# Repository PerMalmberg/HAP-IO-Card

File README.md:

# HAP I/O Card
Input/output card for use in automation

## Design limits
12V maximum voltage.

## Inputs

### Analog inputs

On-board potentiometers as voltage dividers, allowing for adjustable balanced lines used in alarm systems.
> Will fixed resistors do the trick?

### Digital Inputs

* Optocouplers to provide isolation.
* On-board rotary switch to set number of inputs.
* On-board rotary switch to set unit MQTT address.

> Can it be done so that from a software perspective they are always high/true when 'activated'?

## Outputs

### Digital Outputs

* Optocoupler for low current signals.
* Relays for high-current signals.
* Each output shall have a LED indicating current status.

### General in/outputs

UART flashing connectors.
Debugging pins/JTAG

## On-board LEDs
* Power
* Digital outputs
* Digital inputs

## On-board switches
* OTA-enable

## Power supply
12V DC, with onboard 12->5V DC/DC converter.

## Reference Links

http://www.thebox.myzen.co.uk/Tutorial/Protection.html

* Capacitor calculations
  * http://www.electronics-tutorials.ws/rc/rc_1.html

### Components

#### uC ESP32 thing devboard
  * http://www.mouser.se/new/sparkfun/sparkfun-things/

* Common components
  * 10k ohm 0805 0.5W https://www.digikey.se/product-detail/en/panasonic-electronic-components/ERJ-P06F1002V/P16059CT-ND/3982406
  * 100nF 50V https://www.digikey.se/product-detail/en/avx-corporation/08055C104JAT2A/478-3352-1-ND/930144

* Sensor Inputs
  * I/O Expander ADS1115IDGST https://www.digikey.se/product-detail/en/texas-instruments/ADS1115IDGST/296-24934-1-ND/2123298
  * Varistor 39V 0805 https://www.digikey.se/product-detail/en/epcos-tdk/B72510E250K62/495-7453-1-ND/6073112
  * 2k resistor, 0.5W 0805 https://www.digikey.se/product-detail/en/panasonic-electronic-components/ERJ-P06F2001V/P16065CT-ND/3982412
  * Clamping Shottky diodes 60V, 500mA SOD-123 https://www.digikey.se/product-detail/en/stmicroelectronics/STPS0560Z/497-3787-1-ND/691956
  * Protection diode 3A, SMA https://www.digikey.se/product-detail/en/comchip-technology/CDBA3100-HF/641-1747-1-ND/5400721
  * 100 ohm 1/8W 0805 https://www.digikey.se/product-detail/en/yageo/RC0805FR-07100RL/311-100CRCT-ND/730490
  * 1k ohm 0.5W 0805 https://www.digikey.se/product-detail/en/vishay-dale/CRCW08051K00FKEAHP/541-1.00KTCT-ND/2222852

* Digital I/O
  * I/O Expander MCP23017 https://www.digikey.se/product-detail/en/microchip-technology/MCP23017T-E-SO/MCP23017T-E-SOCT-ND/5358289
  * Input      
    * LED Green Vf 2.2, 20mA https://www.digikey.se/product-detail/en/lumex-opto-components-inc/SML-LXR85GC-TR/67-1557-1-ND/304376
    * LED limiting resistor 56R, 1/8W, 0805 https://www.digikey.se/product-detail/en/panasonic-electronic-components/ERJ-6GEYJ560V/P56ACT-ND/42928
    * 100R discharge resistor https://www.digikey.se/product-detail/en/stackpole-electronics-inc/RNCP0805FTD100R/RNCP0805FTD100RCT-ND/2240548
    * 10uF Electrolytic Cap https://www.digikey.se/product-detail/en/panasonic-electronic-components/EEE-1EA100WR/PCE3895CT-ND/766271
    * 1k 3W, 1%, 2512 https://www.digikey.se/product-detail/en/te-connectivity-passive-product/35221K0FT/A121161CT-ND/5245218
    * LTV-354T https://www.digikey.se/product-detail/en/lite-on-inc/LTV-354T/160-1333-1-ND/385797
  * Output
    * Base resistor 470 http://www.digikey.se/scripts/DkSearch/dksus.dll?Detail&itemSeq=230677912&uq=636330538988753686
    * Kickback protection MBR0580 https://www.digikey.se/product-detail/en/micro-commercial-co/MBR0580-TP/MBR0580-TPMSCT-ND/2423306
    * Transistor https://www.digikey.se/product-detail/en/diodes-incorporated/ZXTN25050DFHTA/ZXTN25050DFHCT-ND/1043605
    * LED RED 20mA, Vf 2V https://www.digikey.se/product-detail/en/lumex-opto-components-inc/SML-LXR85IC-TR/67-1556-1-ND/304374
    * LED limiting resistor 68R, 1/8W, 0805 https://www.digikey.se/product-detail/en/stack  pole-electronics-inc/RMCF0805JT68R0/RMCF0805JT68R0CT-ND/1942537

* Power supply
  * Screw terminal 3-way https://www.digikey.se/product-detail/en/te-connectivity-amp-connectors/282834-3/A98334-ND/1153264
  * LM1086-5V https://www.digikey.se/product-detail/en/texas-instruments/LM1086IT-5.0-NOPB/LM1086IT-5.0-NOPB-ND/363580
  * LM1086-3.3V https://www.digikey.se/product-detail/en/texas-instruments/LM1086IT-3.3-NOPB/LM1086IT-3.3-NOPB-ND/363579
  * 100uF 16V 5mm https://www.digikey.se/product-detail/en/nichicon/ULD1C101MED1TD/493-14722-1-ND/6161730
  * Protection diode MBRS360BT3G http://www.digikey.se/scripts/DkSearch/dksus.dll?Detail&itemSeq=230549693&uq=636329621710320791
  * Zener 5.1V SOD-123 https://www.digikey.se/products/en?keywords=1N4733AW-TPMSCT-ND
  * Signal filter https://www.digikey.se/product-detail/en/murata-electronics-north-america/DSS1NB31H104Q91A/490-9806-1-ND/5018359

https://www.facebook.com/groups/SHgruppen/permalink/662561353933301/?comment_id=662612023928234&reply_comment_id=662644947258275&notif_t=group_comment_reply&notif_id=1495821072857152

https://www.facebook.com/groups/SHgruppen/permalink/662561353933301/?comment_id=662622243927212&reply_comment_id=662650937257676&comment_tracking=%7B%22tn%22%3A%22R5%22%7D

## TODO
Fuse 12V and 3.3V PolyFuse

I2C jumpers to disable devices (development feature)?
ESD protection on in/outputs
Display
Flashing wires
Mounting holes http://www.ebay.com/itm/DIN-Rail-Mounting-Carrier-for-72mm-x-110mm-PCB-Housing-Bracket-/131318695142
I2C expansion header
Test points

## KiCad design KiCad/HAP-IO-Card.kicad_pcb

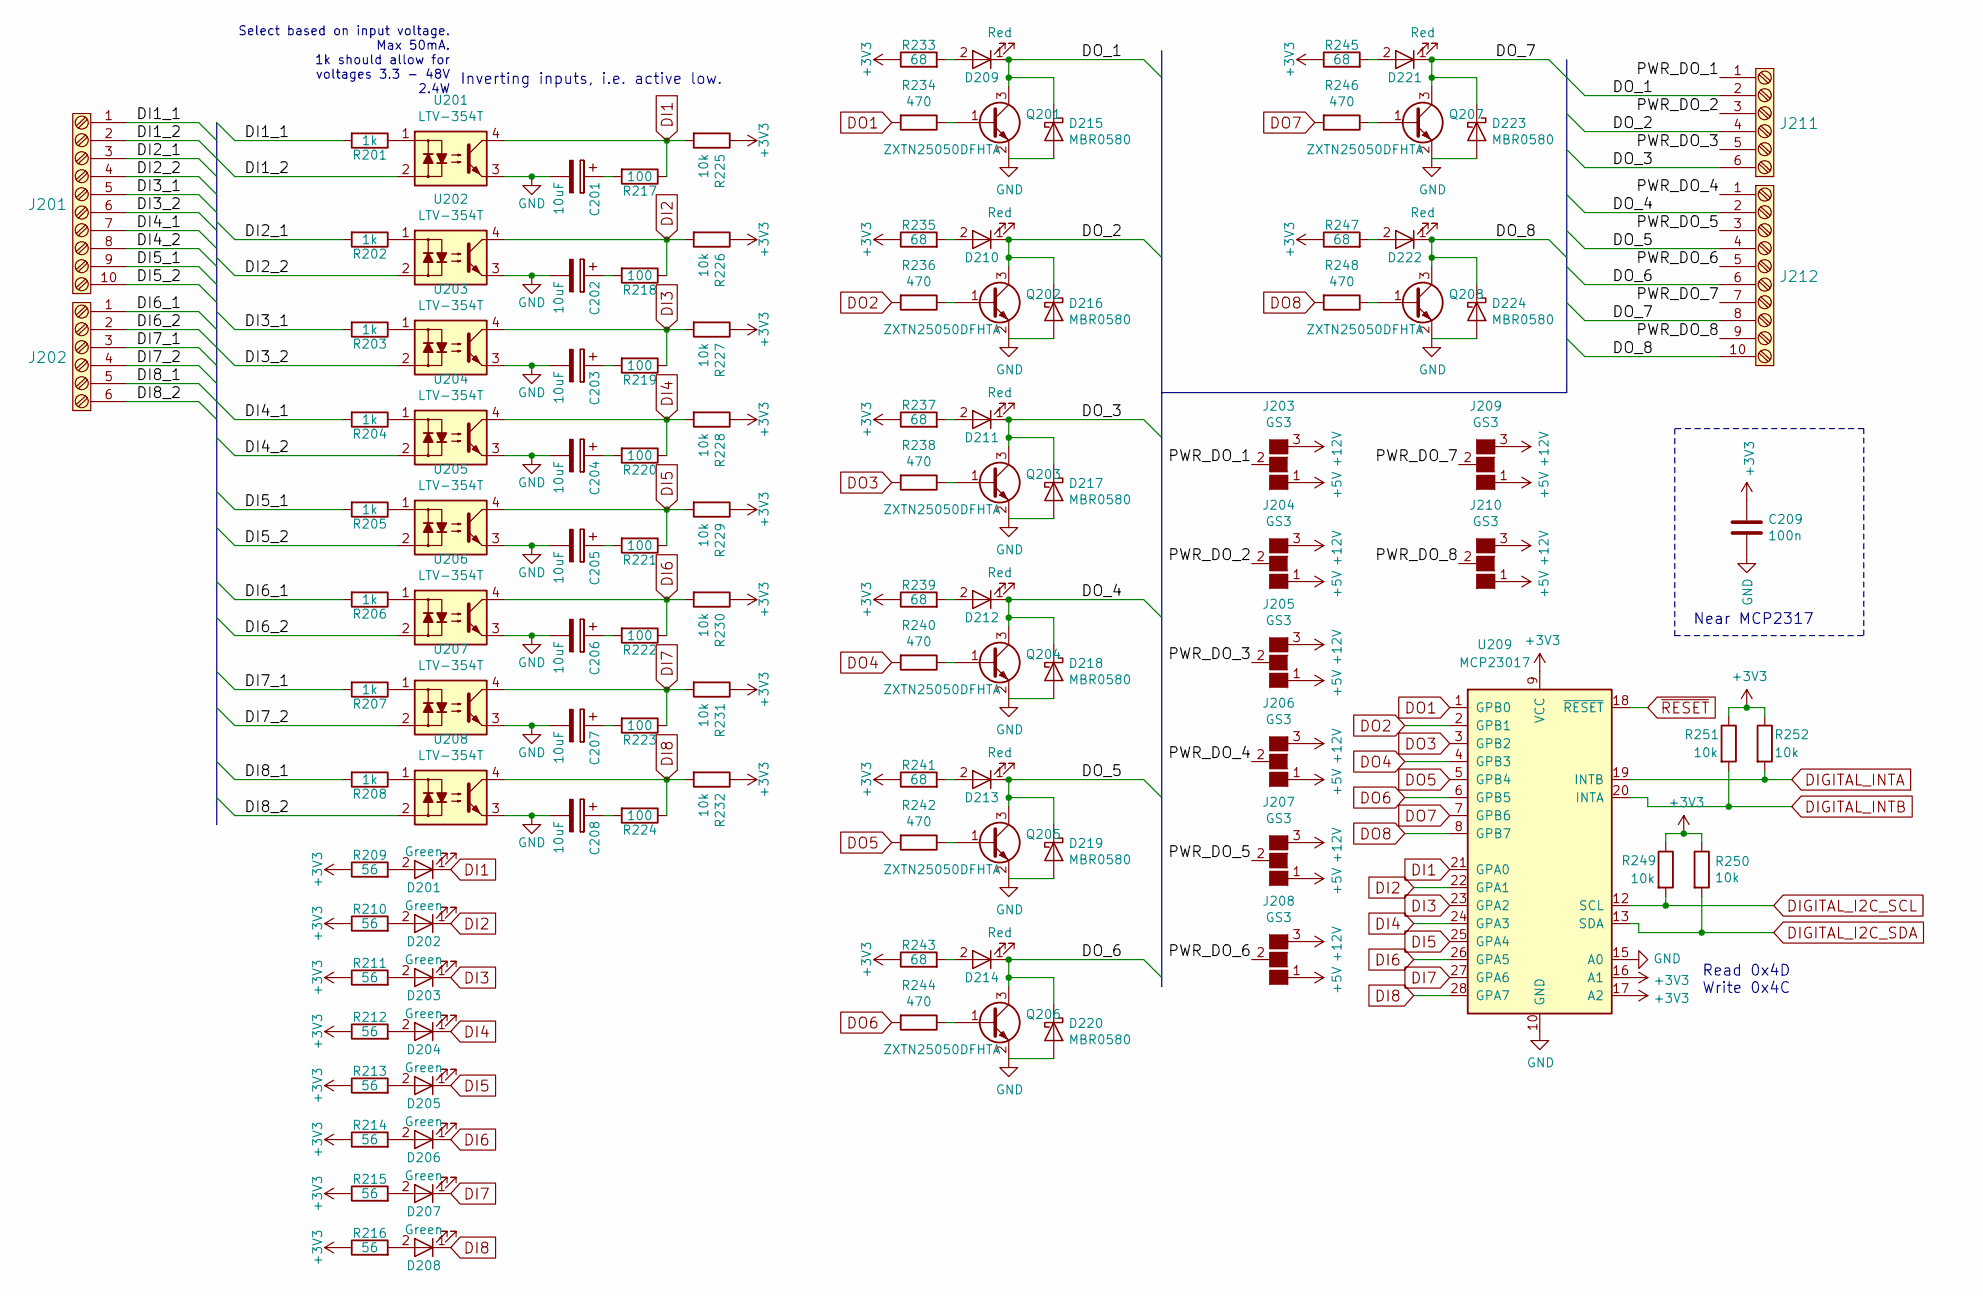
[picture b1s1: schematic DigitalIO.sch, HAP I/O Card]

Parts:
C201, C202, C203, C204, C205, C206, C207, C208: 10uF; CP_Elec_5x4.5
C209: 100n; C_0805
D201, D202, D203, D204, D205, D206, D207, D208: Green; LED_0805
D209, D210, D211, D212, D213, D214, D221, D222: Red; LED_0805
D215, D216, D217, D218, D219, D220, D223, D224: MBR0580; D_SOD-123
J201, J212: TE_Connectivity_1-282834-0
J202, J211: TE_Connectivity_282834-6
J203, J204, J205, J206, J207, J208, J209, J210: GS3
Q201, Q202, Q203, Q204, Q205, Q206, Q207, Q208: ZXTN25050DFHTA; SOT-23
R201, R202, R203, R204, R205, R206, R207, R208: 1k; R_2512
R209, R210, R211, R212, R213, R214, R215, R216: 56; R_0805
R217, R218, R219, R220, R221, R222, R223, R224: 100; R_0805
R225, R226, R227, R228, R229, R230, R231, R232, R249, R250, R251, R252: 10k; R_0805
R233, R235, R237, R239, R241, R243, R245, R247: 68; R_0805
R234, R236, R238, R240, R242, R244, R246, R248: 470; R_0805
U201, U202, U203, U204, U205, U206, U207, U208: LTV-354T; SO-4_4.4x3.6mm_Pitch2.54mm
U209: MCP23017; SOIC-28W_7.5x17.9mm_Pitch1.27mm

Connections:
+12V: J203.3 (G3), J204.3 (G3), J205.3 (G3), J206.3 (G3), J207.3 (G3), J208.3 (G3), J209.3 (G3), J210.3 (G3); also elsewhere on the board
/Digital I/O/DI1_1: J201.1, R201.2
/Digital I/O/DI1_2: J201.2, U201.2
/Digital I/O/DI2_1: J201.3, R202.2
/Digital I/O/DI2_2: J201.4, U202.2
/Digital I/O/DI3_1: J201.5, R203.2
/Digital I/O/DI3_2: J201.6, U203.2
/Digital I/O/DI4_1: J201.7, R204.2
/Digital I/O/DI4_2: J201.8, U204.2
/Digital I/O/DI5_1: J201.9, R205.2
/Digital I/O/DI5_2: J201.10, U205.2
/Digital I/O/DI6_1: J202.1, R206.2
/Digital I/O/DI6_2: J202.2, U206.2
/Digital I/O/DI7_1: J202.3, R207.2
/Digital I/O/DI7_2: J202.4, U207.2
/Digital I/O/DI8_1: J202.5, R208.2
/Digital I/O/DI8_2: J202.6, U208.2
/Digital I/O/DO_1: D209.1 (K), D215.1 (K), J211.2, Q201.3 (C)
/Digital I/O/DO_2: D210.1 (K), D216.1 (K), J211.4, Q202.3 (C)
/Digital I/O/DO_3: D211.1 (K), D217.1 (K), J211.6, Q203.3 (C)
/Digital I/O/DO_4: D212.1 (K), D218.1 (K), J212.2, Q204.3 (C)
/Digital I/O/DO_5: D213.1 (K), D219.1 (K), J212.4, Q205.3 (C)
/Digital I/O/DO_6: D214.1 (K), D220.1 (K), J212.6, Q206.3 (C)
/Digital I/O/DO_7: D221.1 (K), D223.1 (K), J212.8, Q207.3 (C)
/Digital I/O/DO_8: D222.1 (K), D224.1 (K), J212.10, Q208.3 (C)
/Digital I/O/PWR_DO_1: J203.2 (G2), J211.1
/Digital I/O/PWR_DO_2: J204.2 (G2), J211.3
/Digital I/O/PWR_DO_3: J205.2 (G2), J211.5
/Digital I/O/PWR_DO_4: J206.2 (G2), J212.1
/Digital I/O/PWR_DO_5: J207.2 (G2), J212.3
/Digital I/O/PWR_DO_6: J208.2 (G2), J212.5
/Digital I/O/PWR_DO_7: J209.2 (G2), J212.7
/Digital I/O/PWR_DO_8: J210.2 (G2), J212.9
DI1: D201.1 (K), R217.1, R225.2, U201.4, U209.21 (GPA0)
DI2: D202.1 (K), R218.1, R226.2, U202.4, U209.22 (GPA1)
DI3: D203.1 (K), R219.1, R227.2, U203.4, U209.23 (GPA2)
DI4: D204.1 (K), R220.1, R228.2, U204.4, U209.24 (GPA3)
DI5: D205.1 (K), R221.1, R229.2, U205.4, U209.25 (GPA4)
DI6: D206.1 (K), R222.1, R230.2, U206.4, U209.26 (GPA5)
DI7: D207.1 (K), R223.1, R231.2, U207.4, U209.27 (GPA6)
DI8: D208.1 (K), R224.1, R232.2, U208.4, U209.28 (GPA7)
DIGITAL_I2C_SCL: R249.2, U209.12 (SCL); also elsewhere on the board
DIGITAL_I2C_SDA: R250.2, U209.13 (SDA); also elsewhere on the board
DIGITAL_INTA: R252.2, U209.19 (INTB); also elsewhere on the board
DIGITAL_INTB: R251.2, U209.20 (INTA); also elsewhere on the board
DO1: R234.2, U209.1 (GPB0)
DO2: R236.2, U209.2 (GPB1)
DO3: R238.2, U209.3 (GPB2)
DO4: R240.2, U209.4 (GPB3)
DO5: R242.2, U209.5 (GPB4)
DO6: R244.2, U209.6 (GPB5)
DO7: R246.2, U209.7 (GPB6)
DO8: R248.2, U209.8 (GPB7)
Earth: C201.2, C202.2, C203.2, C204.2, C205.2, C206.2, C207.2, C208.2, C209.2, D215.2 (A), D216.2 (A), D217.2 (A), D218.2 (A), D219.2 (A), D220.2 (A), D223.2 (A), D224.2 (A), Q201.2 (E), Q202.2 (E), Q203.2 (E), Q204.2 (E), Q205.2 (E), Q206.2 (E), Q207.2 (E), Q208.2 (E), U201.3, U202.3, U203.3, U204.3, U205.3, U206.3, U207.3, U208.3, U209.10 (GND), U209.15 (A0); also elsewhere on the board
unnamed: C201.1, R217.2
unnamed: C202.1, R218.2
unnamed: C203.1, R219.2
unnamed: C204.1, R220.2
unnamed: C205.1, R221.2
unnamed: C206.1, R222.2
unnamed: C207.1, R223.2
unnamed: C208.1, R224.2
unnamed: D201.2 (A), R209.2
unnamed: D202.2 (A), R210.2
unnamed: D203.2 (A), R211.2
unnamed: D204.2 (A), R212.2
unnamed: D205.2 (A), R213.2
unnamed: D206.2 (A), R214.2
unnamed: D207.2 (A), R215.2
unnamed: D208.2 (A), R216.2
unnamed: D209.2 (A), R233.2
unnamed: D210.2 (A), R235.2
unnamed: D211.2 (A), R237.2
unnamed: D212.2 (A), R239.2
unnamed: D213.2 (A), R241.2
unnamed: D214.2 (A), R243.2
unnamed: D221.2 (A), R245.2
unnamed: D222.2 (A), R247.2
unnamed: Q201.1 (B), R234.1
unnamed: Q202.1 (B), R236.1
unnamed: Q203.1 (B), R238.1
unnamed: Q204.1 (B), R240.1
unnamed: Q205.1 (B), R242.1
unnamed: Q206.1 (B), R244.1
unnamed: Q207.1 (B), R246.1
unnamed: Q208.1 (B), R248.1
unnamed: R201.1, U201.1
unnamed: R202.1, U202.1
unnamed: R203.1, U203.1
unnamed: R204.1, U204.1
unnamed: R205.1, U205.1
unnamed: R206.1, U206.1
unnamed: R207.1, U207.1
unnamed: R208.1, U208.1
POWER3V3: C209.1, R209.1, R210.1, R211.1, R212.1, R213.1, R214.1, R215.1, R216.1, R225.1, R226.1, R227.1, R228.1, R229.1, R230.1, R231.1, R232.1, R233.1, R235.1, R237.1, R239.1, R241.1, R243.1, R245.1, R247.1, R249.1, R250.1, R251.1, R252.1, U209.9 (VCC), U209.16 (A1), U209.17 (A2); also elsewhere on the board
POWER5V: J203.1 (G1), J204.1 (G1), J205.1 (G1), J206.1 (G1), J207.1 (G1), J208.1 (G1), J209.1 (G1), J210.1 (G1); also elsewhere on the board
~RESET: U209.18 (~RESET); also elsewhere on the board

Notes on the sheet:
Select based on input voltage. Max 50mA. 1k should allow for voltages 3.3 - 48V 2.4W
Inverting inputs, i.e. active low.
Read 0x4D Write 0x4C
Near MCP2317

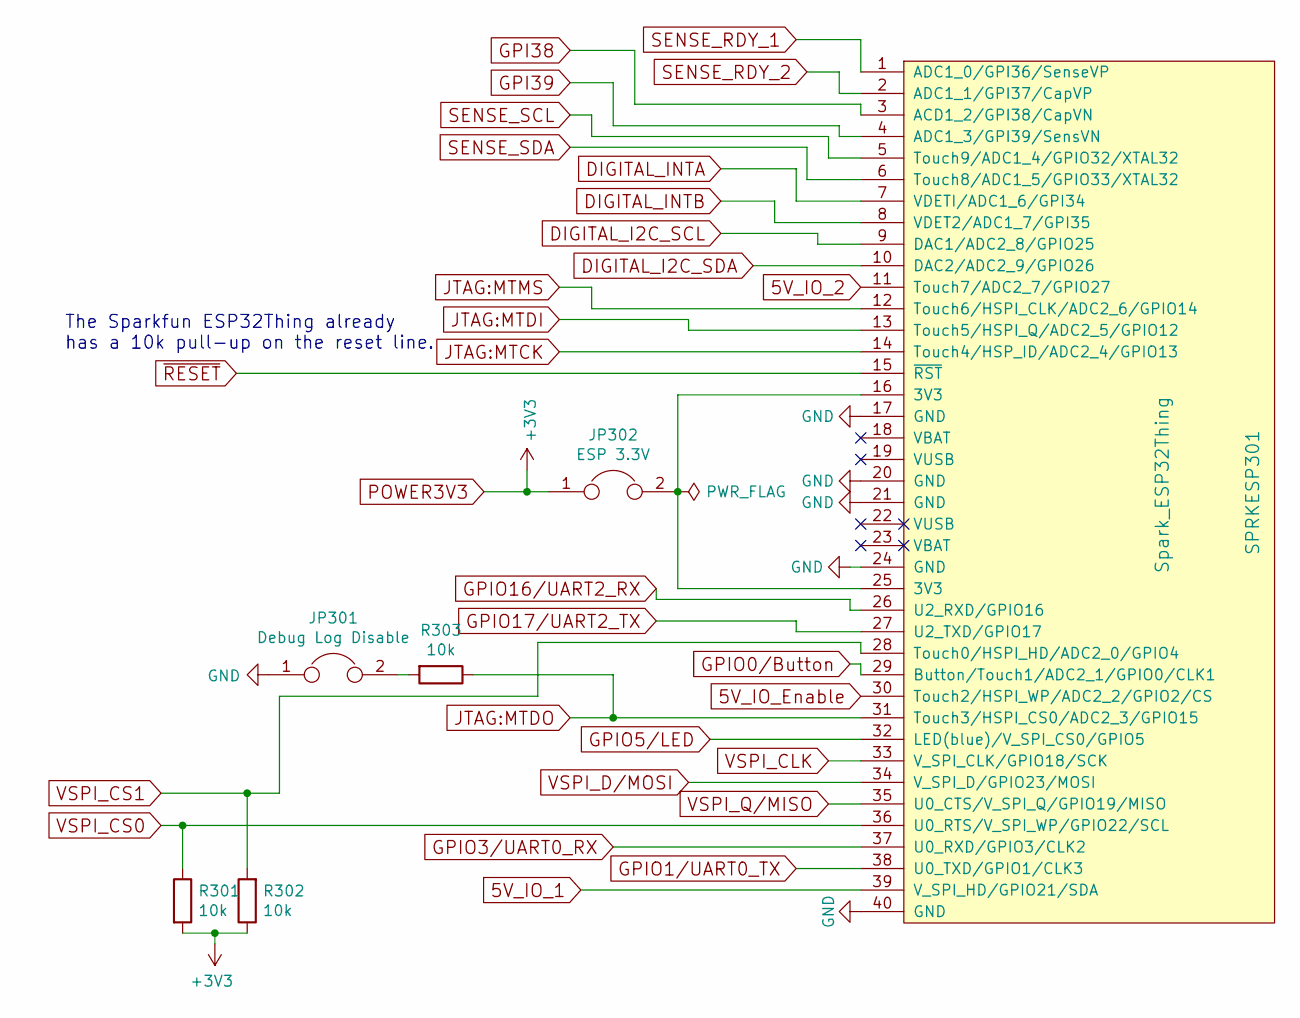
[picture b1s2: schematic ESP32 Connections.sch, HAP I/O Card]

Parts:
JP301: Debug Log Disable; Pin_Header_Straight_1x02_Pitch2.54mm
JP302: ESP 3.3V; Pin_Header_Straight_1x02_Pitch2.54mm
R301, R302, R303: 10k; R_0805
SPRKESP301: Spark_ESP32Thing; Sparkfun_ESP32Thing

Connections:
5V_IO_1: SPRKESP301.39 (V_SPI_HD/GPIO21/SDA); also elsewhere on the board
5V_IO_2: SPRKESP301.11 (Touch7/ADC2_7/GPIO27); also elsewhere on the board
5V_IO_Enable: SPRKESP301.30 (Touch2/HSPI_WP/ADC2_2/GPIO2/CS); also elsewhere on the board
DIGITAL_I2C_SCL: SPRKESP301.9 (DAC1/ADC2_8/GPIO25); also elsewhere on the board
DIGITAL_I2C_SDA: SPRKESP301.10 (DAC2/ADC2_9/GPIO26); also elsewhere on the board
DIGITAL_INTA: SPRKESP301.7 (VDETI/ADC1_6/GPI34); also elsewhere on the board
DIGITAL_INTB: SPRKESP301.8 (VDET2/ADC1_7/GPI35); also elsewhere on the board
Earth: JP301.1, SPRKESP301.17 (GND), SPRKESP301.20 (GND), SPRKESP301.21 (GND), SPRKESP301.24 (GND), SPRKESP301.40 (GND); also elsewhere on the board
GPI38: SPRKESP301.3 (ACD1_2/GPI38/CapVN); also elsewhere on the board
GPI39: SPRKESP301.4 (ADC1_3/GPI39/SensVN); also elsewhere on the board
GPIO0/Button: SPRKESP301.29 (Button/Touch1/ADC2_1/GPIO0/CLK1); also elsewhere on the board
GPIO1/UART0_TX: SPRKESP301.38 (U0_TXD/GPIO1/CLK3); also elsewhere on the board
GPIO3/UART0_RX: SPRKESP301.37 (U0_RXD/GPIO3/CLK2); also elsewhere on the board
GPIO5/LED: SPRKESP301.32 (LED(blue)/V_SPI_CS0/GPIO5); also elsewhere on the board
GPIO16/UART2_RX: SPRKESP301.26 (U2_RXD/GPIO16); also elsewhere on the board
GPIO17/UART2_TX: SPRKESP301.27 (U2_TXD/GPIO17); also elsewhere on the board
JTAG:MTCK: SPRKESP301.14 (Touch4/HSP_ID/ADC2_4/GPIO13); also elsewhere on the board
JTAG:MTDI: SPRKESP301.13 (Touch5/HSPI_Q/ADC2_5/GPIO12); also elsewhere on the board
JTAG:MTDO: R303.1, SPRKESP301.31 (Touch3/HSPI_CS0/ADC2_3/GPIO15); also elsewhere on the board
JTAG:MTMS: SPRKESP301.12 (Touch6/HSPI_CLK/ADC2_6/GPIO14); also elsewhere on the board
unnamed: JP301.2, R303.2
unnamed: JP302.2, SPRKESP301.16 (3V3), SPRKESP301.25 (3V3)
POWER3V3: JP302.1, R301.2, R302.1; also elsewhere on the board
SENSE_RDY_1: SPRKESP301.1 (ADC1_0/GPI36/SenseVP); also elsewhere on the board
SENSE_RDY_2: SPRKESP301.2 (ADC1_1/GPI37/CapVP); also elsewhere on the board
SENSE_SCL: SPRKESP301.5 (Touch9/ADC1_4/GPIO32/XTAL32); also elsewhere on the board
SENSE_SDA: SPRKESP301.6 (Touch8/ADC1_5/GPIO33/XTAL32); also elsewhere on the board
VSPI_CLK: SPRKESP301.33 (V_SPI_CLK/GPIO18/SCK); also elsewhere on the board
VSPI_CS0: R301.1, SPRKESP301.36 (U0_RTS/V_SPI_WP/GPIO22/SCL); also elsewhere on the board
VSPI_CS1: R302.2, SPRKESP301.28 (Touch0/HSPI_HD/ADC2_0/GPIO4); also elsewhere on the board
VSPI_D/MOSI: SPRKESP301.34 (V_SPI_D/GPIO23/MOSI); also elsewhere on the board
VSPI_Q/MISO: SPRKESP301.35 (U0_CTS/V_SPI_Q/GPIO19/MISO); also elsewhere on the board
~RESET: SPRKESP301.15 (~RST); also elsewhere on the board

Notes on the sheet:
The Sparkfun ESP32Thing already has a 10k pull-up on the reset line.

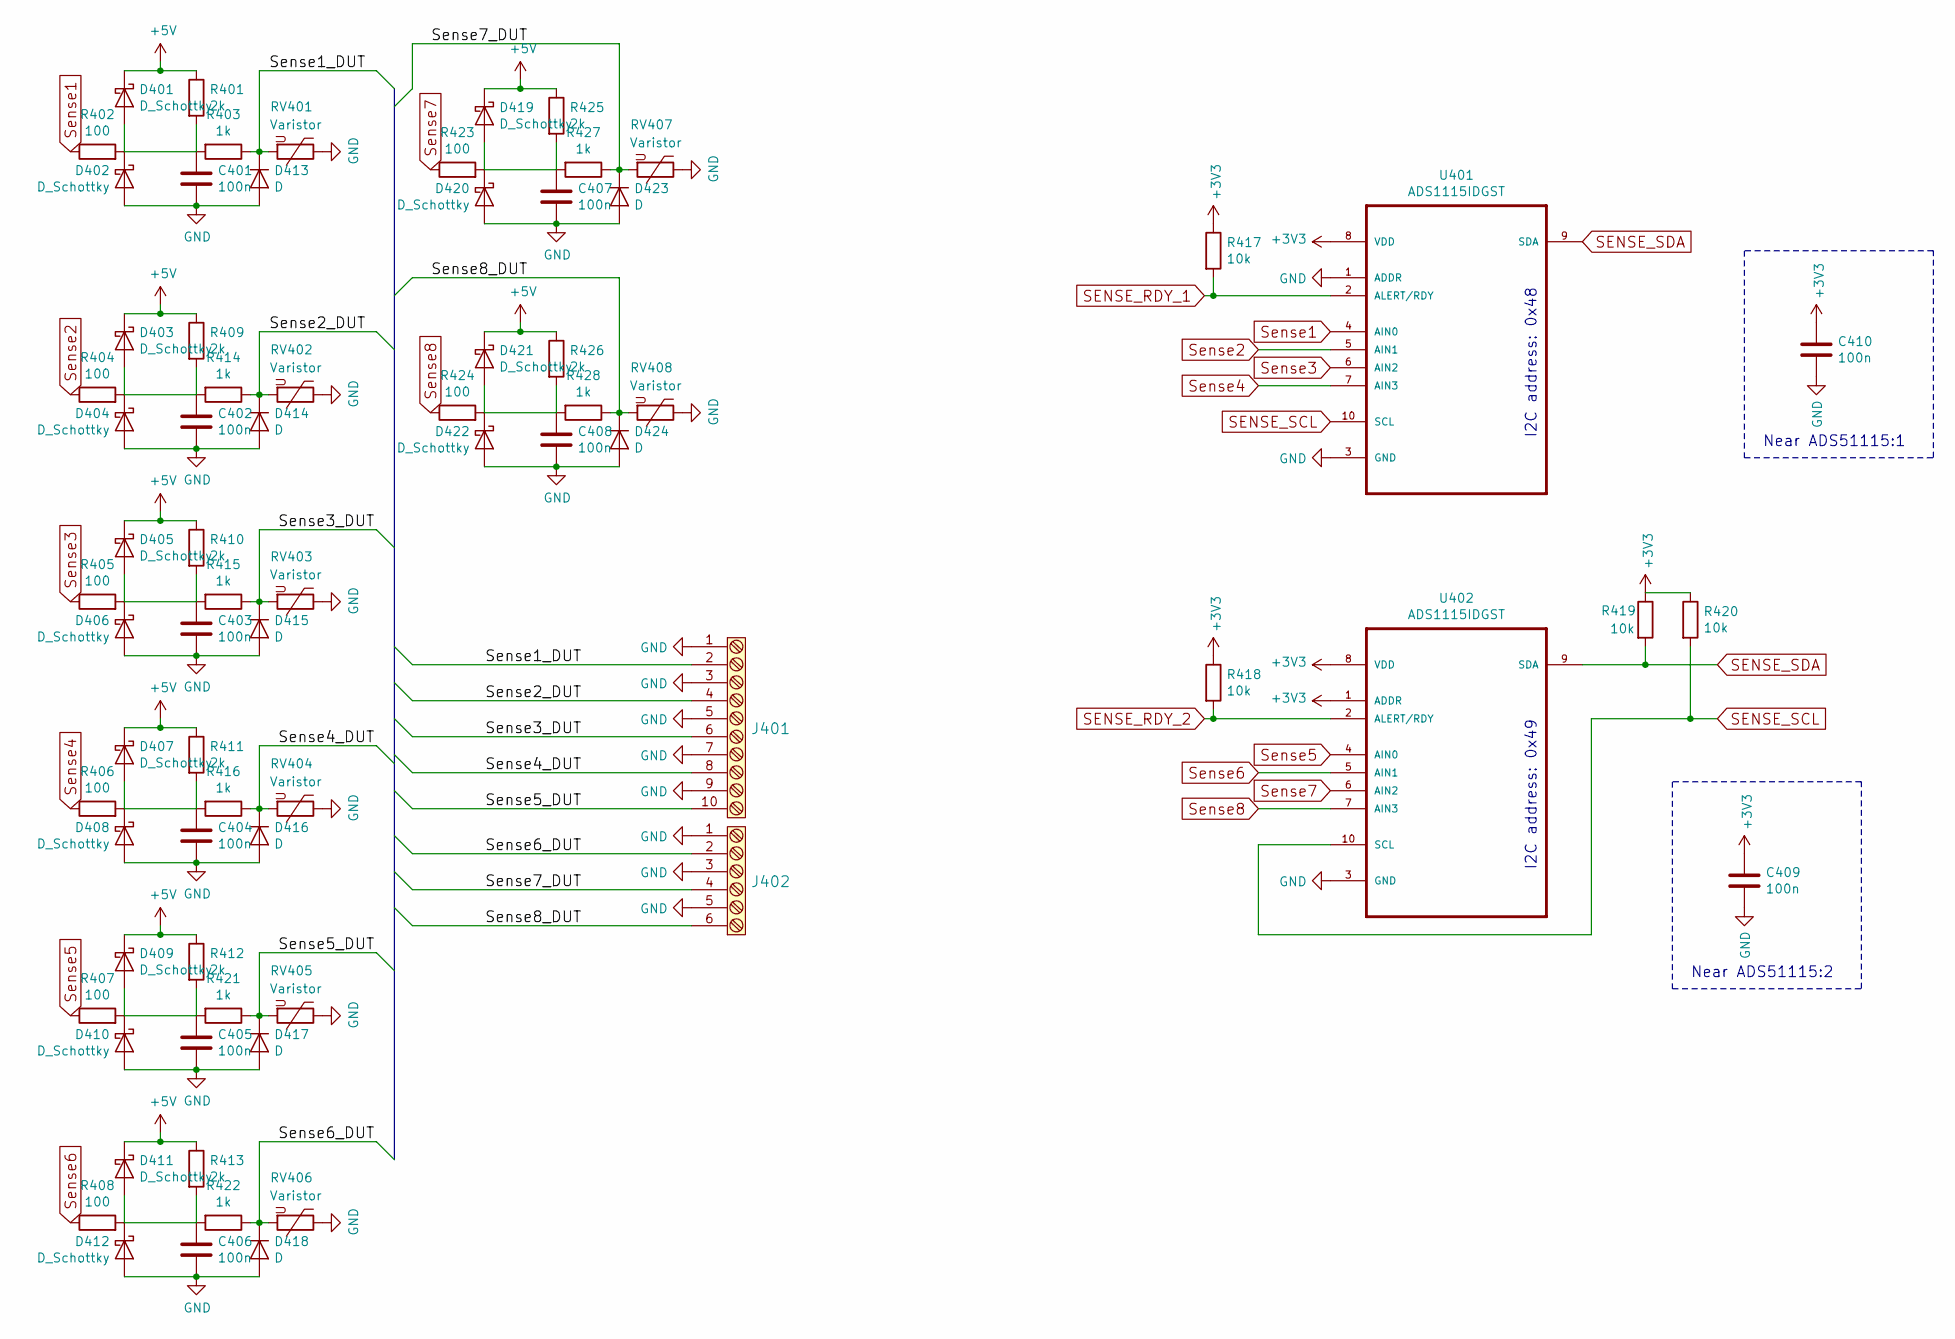
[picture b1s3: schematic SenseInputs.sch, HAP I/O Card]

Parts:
C401, C402, C403, C404, C405, C406, C407, C408, C409, C410: 100n; C_0805
D401, D402, D403, D404, D405, D406, D407, D408, D409, D410, D411, D412, D419, D420, D421, D422: D_Schottky; D_SOD-123
D413, D414, D415, D416, D417, D418, D423, D424: D; D_SMA
J401: TE_Connectivity_1-282834-0
J402: TE_Connectivity_282834-6
R401, R409, R410, R411, R412, R413, R425, R426: 2k; R_0805
R402, R404, R405, R406, R407, R408, R423, R424: 100; R_0805
R403, R414, R415, R416, R421, R422, R427, R428: 1k; R_0805
R417, R418, R419, R420: 10k; R_0805
RV401, RV402, RV403, RV404, RV405, RV406, RV407, RV408: Varistor; R_0805
U401, U402: ADS1115IDGST; SOP50P490X110-10N

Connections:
/Sense Inputs/Sense1_DUT: D413.1 (K), J401.2, R403.1, RV401.2
/Sense Inputs/Sense2_DUT: D414.1 (K), J401.4, R414.1, RV402.2
/Sense Inputs/Sense3_DUT: D415.1 (K), J401.6, R415.1, RV403.2
/Sense Inputs/Sense4_DUT: D416.1 (K), J401.8, R416.1, RV404.2
/Sense Inputs/Sense5_DUT: D417.1 (K), J401.10, R421.1, RV405.2
/Sense Inputs/Sense6_DUT: D418.1 (K), J402.2, R422.1, RV406.2
/Sense Inputs/Sense7_DUT: D423.1 (K), J402.4, R427.1, RV407.2
/Sense Inputs/Sense8_DUT: D424.1 (K), J402.6, R428.1, RV408.2
Earth: C401.1, C402.1, C403.1, C404.1, C405.1, C406.1, C407.1, C408.1, C409.2, C410.2, D402.2 (A), D404.2 (A), D406.2 (A), D408.2 (A), D410.2 (A), D412.2 (A), D413.2 (A), D414.2 (A), D415.2 (A), D416.2 (A), D417.2 (A), D418.2 (A), D420.2 (A), D422.2 (A), D423.2 (A), D424.2 (A), J401.1, J401.3, J401.5, J401.7, J401.9, J402.1, J402.3, J402.5, RV401.1, RV402.1, RV403.1, RV404.1, RV405.1, RV406.1, RV407.1, RV408.1, U401.1 (ADDR), U401.3 (GND), U402.3 (GND); also elsewhere on the board
unnamed: C401.2, D401.2 (A), D402.1 (K), R401.2, R402.2, R403.2
unnamed: C402.2, D403.2 (A), D404.1 (K), R404.2, R409.2, R414.2
unnamed: C403.2, D405.2 (A), D406.1 (K), R405.2, R410.2, R415.2
unnamed: C404.2, D407.2 (A), D408.1 (K), R406.2, R411.2, R416.2
unnamed: C405.2, D409.2 (A), D410.1 (K), R407.2, R412.2, R421.2
unnamed: C406.2, D411.2 (A), D412.1 (K), R408.2, R413.2, R422.2
unnamed: C407.2, D419.2 (A), D420.1 (K), R423.2, R425.2, R427.2
unnamed: C408.2, D421.2 (A), D422.1 (K), R424.2, R426.2, R428.2
POWER3V3: C409.1, C410.1, R417.1, R418.1, R419.1, R420.1, U401.8 (VDD), U402.1 (ADDR), U402.8 (VDD); also elsewhere on the board
POWER5V: D401.1 (K), D403.1 (K), D405.1 (K), D407.1 (K), D409.1 (K), D411.1 (K), D419.1 (K), D421.1 (K), R401.1, R409.1, R410.1, R411.1, R412.1, R413.1, R425.1, R426.1; also elsewhere on the board
SENSE_RDY_1: R417.2, U401.2 (ALERT/RDY); also elsewhere on the board
SENSE_RDY_2: R418.2, U402.2 (ALERT/RDY); also elsewhere on the board
SENSE_SCL: R420.2, U401.10 (SCL), U402.10 (SCL); also elsewhere on the board
SENSE_SDA: R419.2, U401.9 (SDA), U402.9 (SDA); also elsewhere on the board
Sense1: R402.1, U401.4 (AIN0)
Sense2: R404.1, U401.5 (AIN1)
Sense3: R405.1, U401.6 (AIN2)
Sense4: R406.1, U401.7 (AIN3)
Sense5: R407.1, U402.4 (AIN0)
Sense6: R408.1, U402.5 (AIN1)
Sense7: R423.1, U402.6 (AIN2)
Sense8: R424.1, U402.7 (AIN3)

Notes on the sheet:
Near ADS51115:1
Near ADS51115:2
I2C address: 0x48
I2C address: 0x49

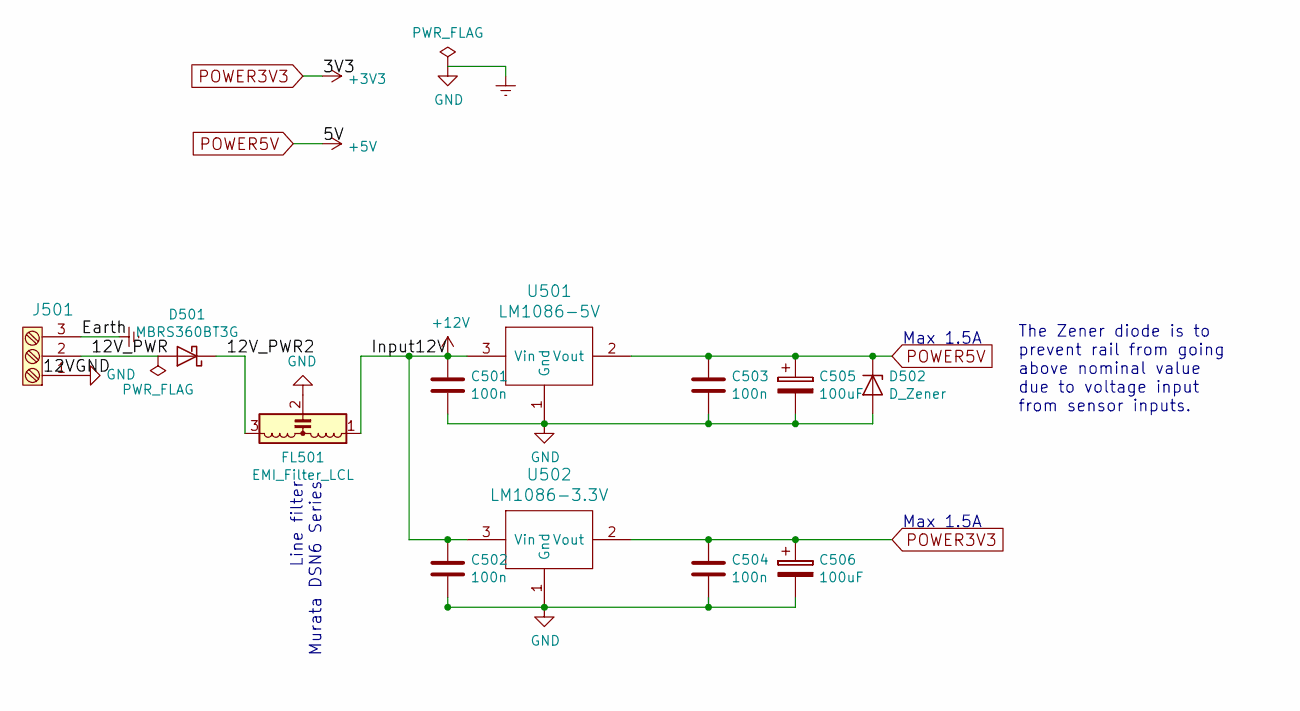
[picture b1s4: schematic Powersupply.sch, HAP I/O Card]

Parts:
C501, C502, C503, C504: 100n; C_0805
C505, C506: 100uF; CP_Radial_D6.3mm_P2.50mm
D501: MBRS360BT3G; D_SMB
D502: D_Zener; D_SOD-123
FL501: EMI_Filter_LCL; Pin_Header_Straight_1x03_Pitch2.54mm
J501: TE_Connectivity_282834-3
U501: LM1086-5V; TO-220_Vertical
U502: LM1086-3.3V; TO-220_Vertical

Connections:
+12V: C501.1, C502.1, FL501.1, U501.3 (Vin), U502.3 (Vin); also elsewhere on the board
/Powersupply/12V_PWR: D501.2 (A), J501.2
/Powersupply/12V_PWR2: D501.1 (K), FL501.3
Earth: C501.2, C502.2, C503.2, C504.2, C505.2, C506.2, D502.2 (A), FL501.2, J501.1, J501.3, U501.1 (Gnd), U502.1 (Gnd); also elsewhere on the board
POWER3V3: C504.1, C506.1, U502.2 (Vout); also elsewhere on the board
POWER5V: C503.1, C505.1, D502.1 (K), U501.2 (Vout); also elsewhere on the board

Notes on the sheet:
Max 1.5A
Line filter Murata DSN6 Series
The Zener diode is to prevent rail from going above nominal value due to voltage input from sensor inputs.

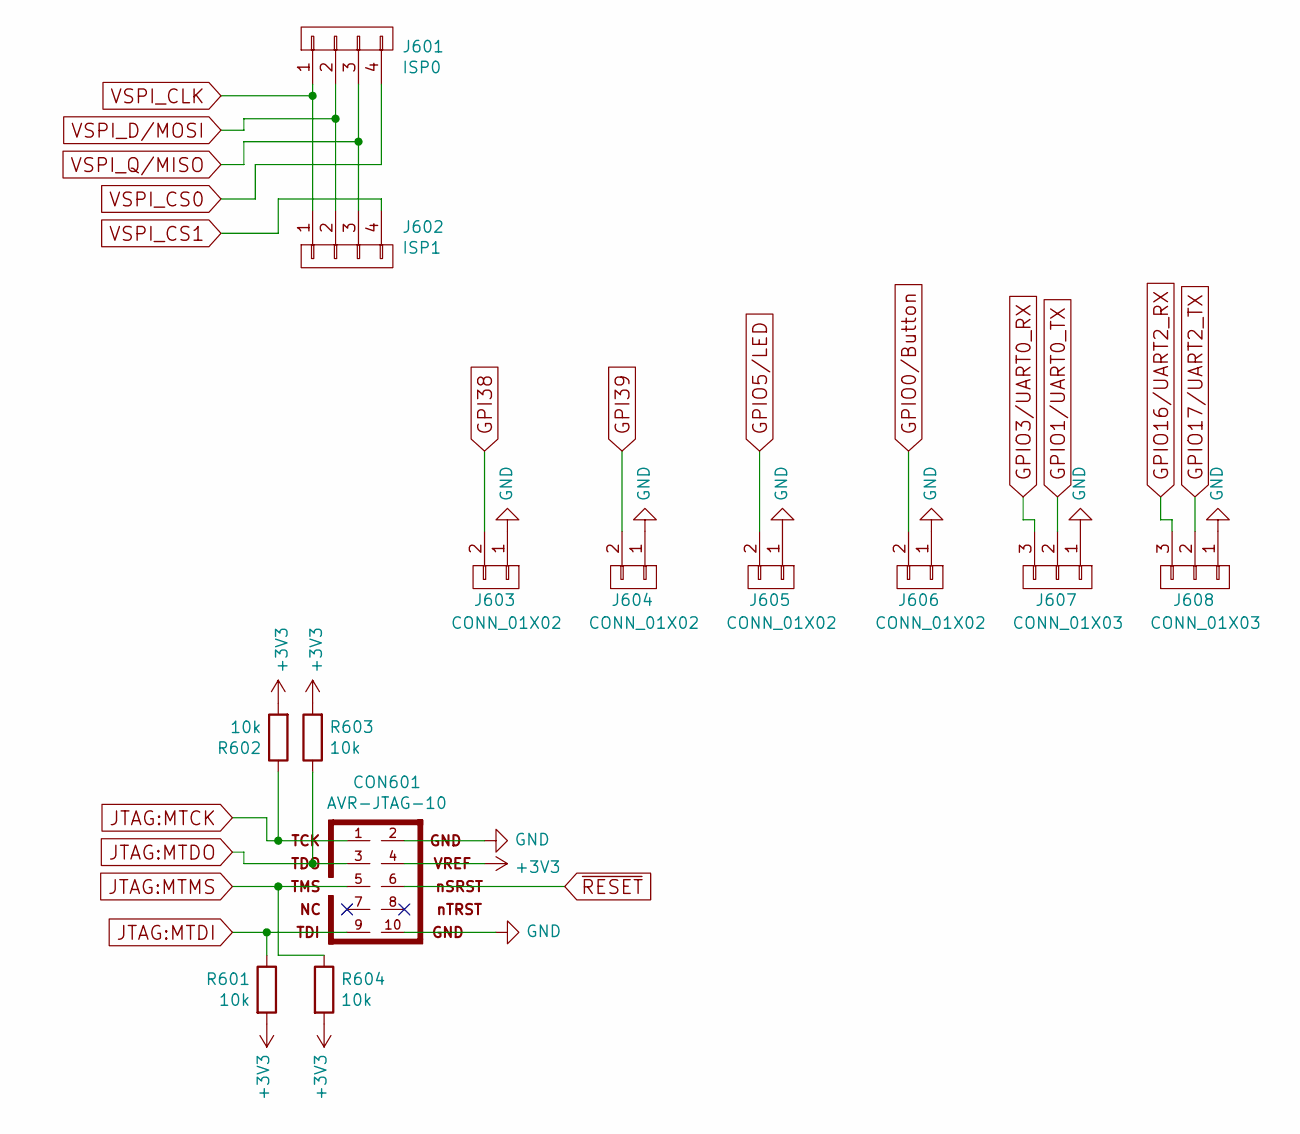
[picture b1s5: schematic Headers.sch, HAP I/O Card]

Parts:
CON601: AVR-JTAG-10; Pin_Header_Straight_2x05_Pitch2.54mm
J601: ISP0; Pin_Header_Straight_1x04_Pitch2.54mm
J602: ISP1; Pin_Header_Straight_1x04_Pitch2.54mm
J603, J604, J605, J606: CONN_01X02; Pin_Header_Straight_1x02_Pitch2.54mm
J607, J608: CONN_01X03; Pin_Header_Straight_1x03_Pitch2.54mm
R601, R602, R603, R604: 10k; R_0805

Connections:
Earth: CON601.2, CON601.10, J603.1, J604.1, J605.1, J606.1, J607.1, J608.1; also elsewhere on the board
GPI38: J603.2; also elsewhere on the board
GPI39: J604.2; also elsewhere on the board
GPIO0/Button: J606.2; also elsewhere on the board
GPIO1/UART0_TX: J607.2; also elsewhere on the board
GPIO3/UART0_RX: J607.3; also elsewhere on the board
GPIO5/LED: J605.2; also elsewhere on the board
GPIO16/UART2_RX: J608.3; also elsewhere on the board
GPIO17/UART2_TX: J608.2; also elsewhere on the board
JTAG:MTCK: CON601.1, R602.1; also elsewhere on the board
JTAG:MTDI: CON601.9, R601.1; also elsewhere on the board
JTAG:MTDO: CON601.3, R603.1; also elsewhere on the board
JTAG:MTMS: CON601.5, R604.1; also elsewhere on the board
POWER3V3: CON601.4, R601.2, R602.2, R603.2, R604.2; also elsewhere on the board
VSPI_CLK: J601.1, J602.1; also elsewhere on the board
VSPI_CS0: J601.4; also elsewhere on the board
VSPI_CS1: J602.4; also elsewhere on the board
VSPI_D/MOSI: J601.2, J602.2; also elsewhere on the board
VSPI_Q/MISO: J601.3, J602.3; also elsewhere on the board
~RESET: CON601.6; also elsewhere on the board

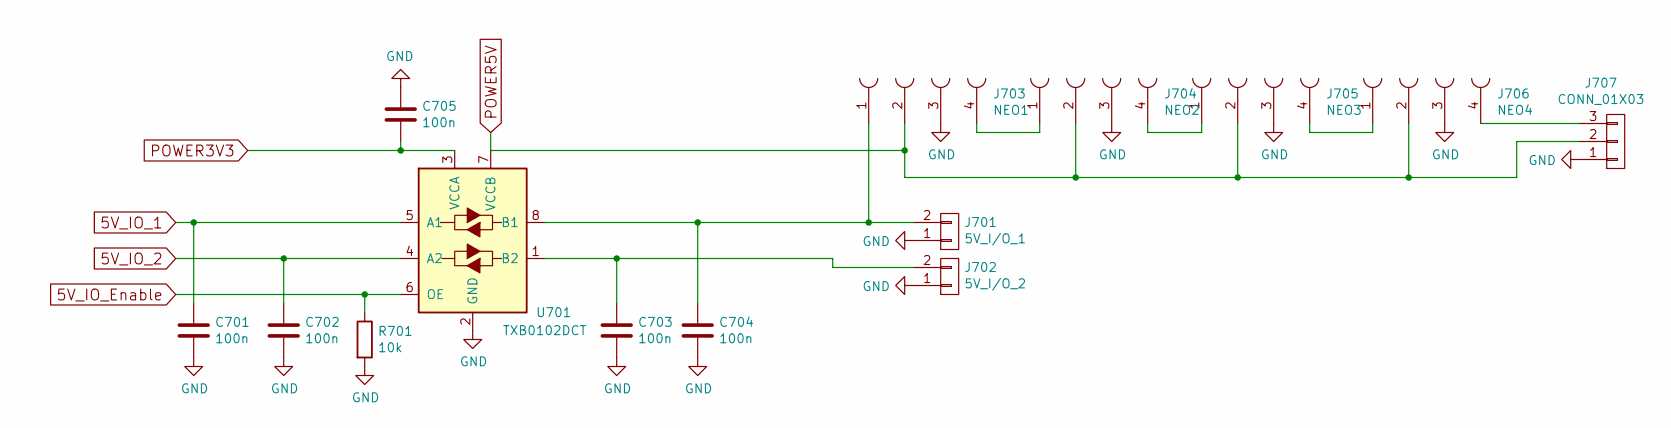
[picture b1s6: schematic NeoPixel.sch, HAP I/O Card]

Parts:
C701, C702, C703, C704, C705: 100n; C_0805
J701: 5V_I/O_1; Pin_Header_Straight_1x02_Pitch2.54mm
J702: 5V_I/O_2; Pin_Header_Straight_1x02_Pitch2.54mm
J703: NEO1; Pin_Header_Straight_1x04_Pitch1.27mm
J704: NEO2; Pin_Header_Straight_1x04_Pitch1.27mm
J705: NEO3; Pin_Header_Straight_1x04_Pitch1.27mm
J706: NEO4; Pin_Header_Straight_1x04_Pitch1.27mm
J707: CONN_01X03; Pin_Header_Straight_1x03_Pitch2.54mm
R701: 10k; R_0805
U701: TXB0102DCT; TSSOP-8_3x3mm_Pitch0.65mm

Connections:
5V_IO_1: C701.1, U701.5 (A1); also elsewhere on the board
5V_IO_2: C702.1, U701.4 (A2); also elsewhere on the board
5V_IO_Enable: R701.1, U701.6 (OE); also elsewhere on the board
Earth: C701.2, C702.2, C703.2, C704.2, C705.1, J701.1, J702.1, J703.3, J704.3, J705.3, J706.3, J707.1, R701.2, U701.2 (GND); also elsewhere on the board
unnamed: C703.1, J702.2, U701.1 (B2)
unnamed: C704.1, J701.2, J703.1, U701.8 (B1)
unnamed: J703.4, J704.1
unnamed: J704.4, J705.1
unnamed: J705.4, J706.1
unnamed: J706.4, J707.3
POWER3V3: C705.2, U701.3 (VCCA); also elsewhere on the board
POWER5V: J703.2, J704.2, J705.2, J706.2, J707.2, U701.7 (VCCB); also elsewhere on the board

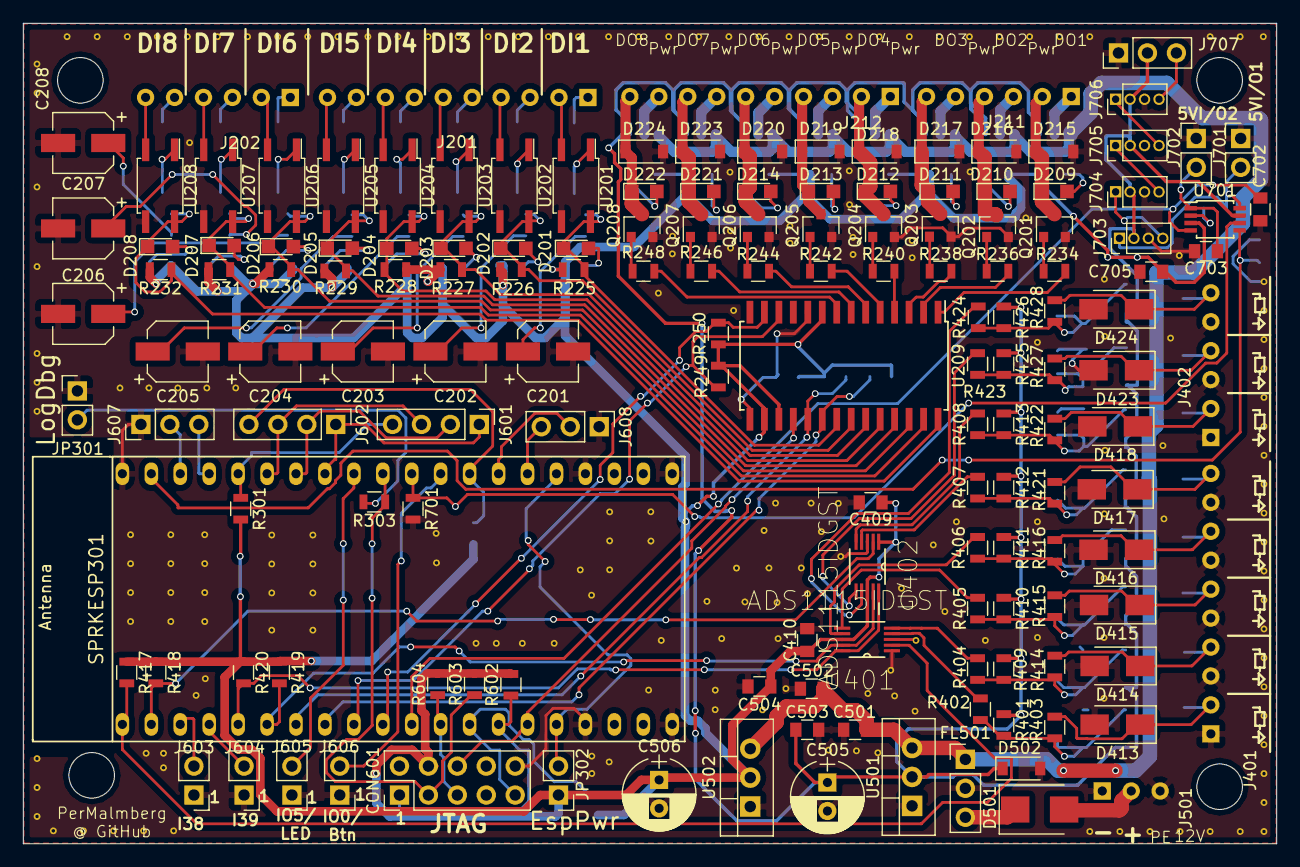
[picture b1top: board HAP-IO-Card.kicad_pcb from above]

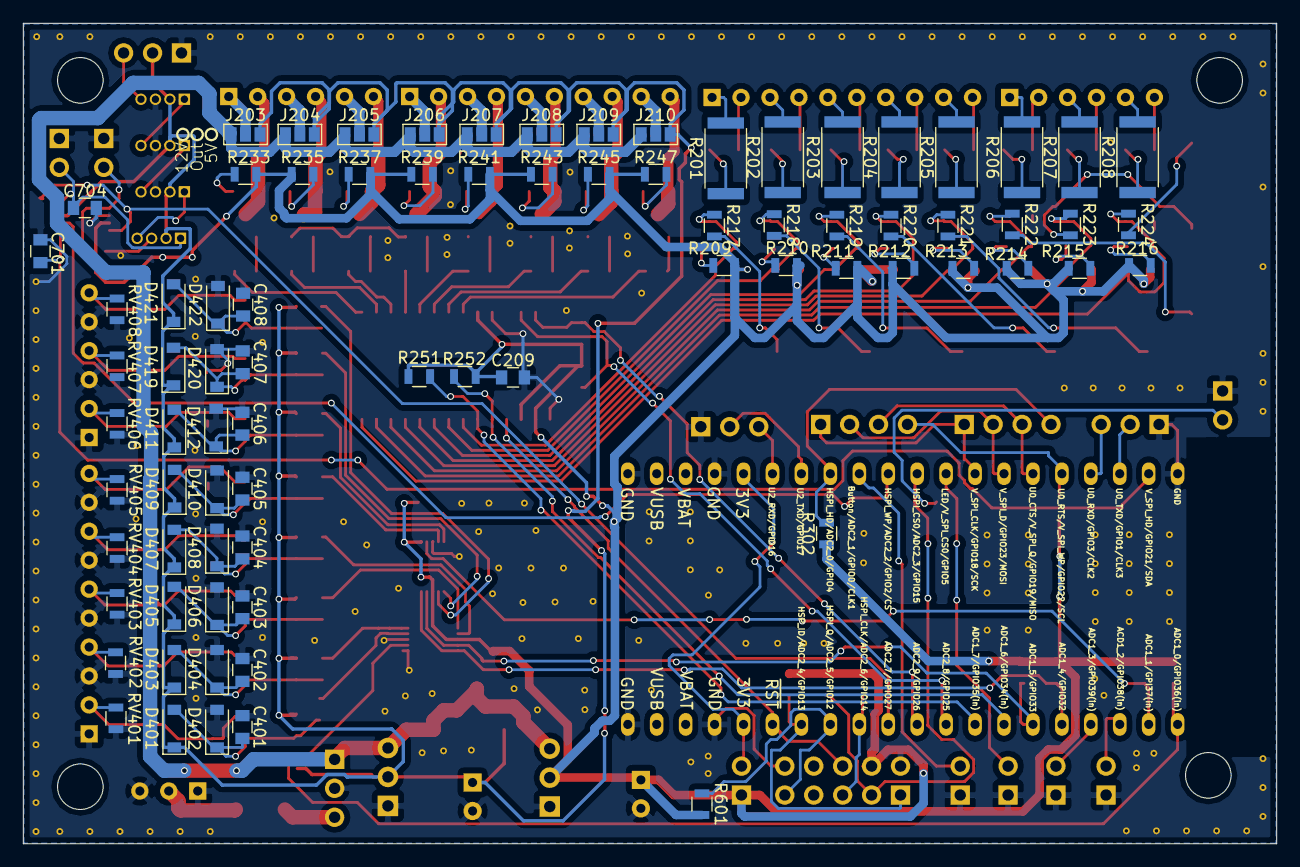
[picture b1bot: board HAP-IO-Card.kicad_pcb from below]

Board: 2 copper layers, 110.0 x 72.0 mm, 233 parts (79 on the bottom side), 155 nets.
